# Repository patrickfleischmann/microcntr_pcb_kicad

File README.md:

# microcntr_pcb_kicad
PCB design files KiCad

[Kicanvas](https://kicanvas.org/?github=https%3A%2F%2Fgithub.com%2Fpatrickfleischmann%2Fmicrocntr_pcb_kicad%2Fblob%2F93434b71915ae8d7c4e8ab5cd5c0984640eee6fc%2Fmicrocntr.kicad_sch)

Application: KiCad (64-bit), Version: (6.0.7), release build

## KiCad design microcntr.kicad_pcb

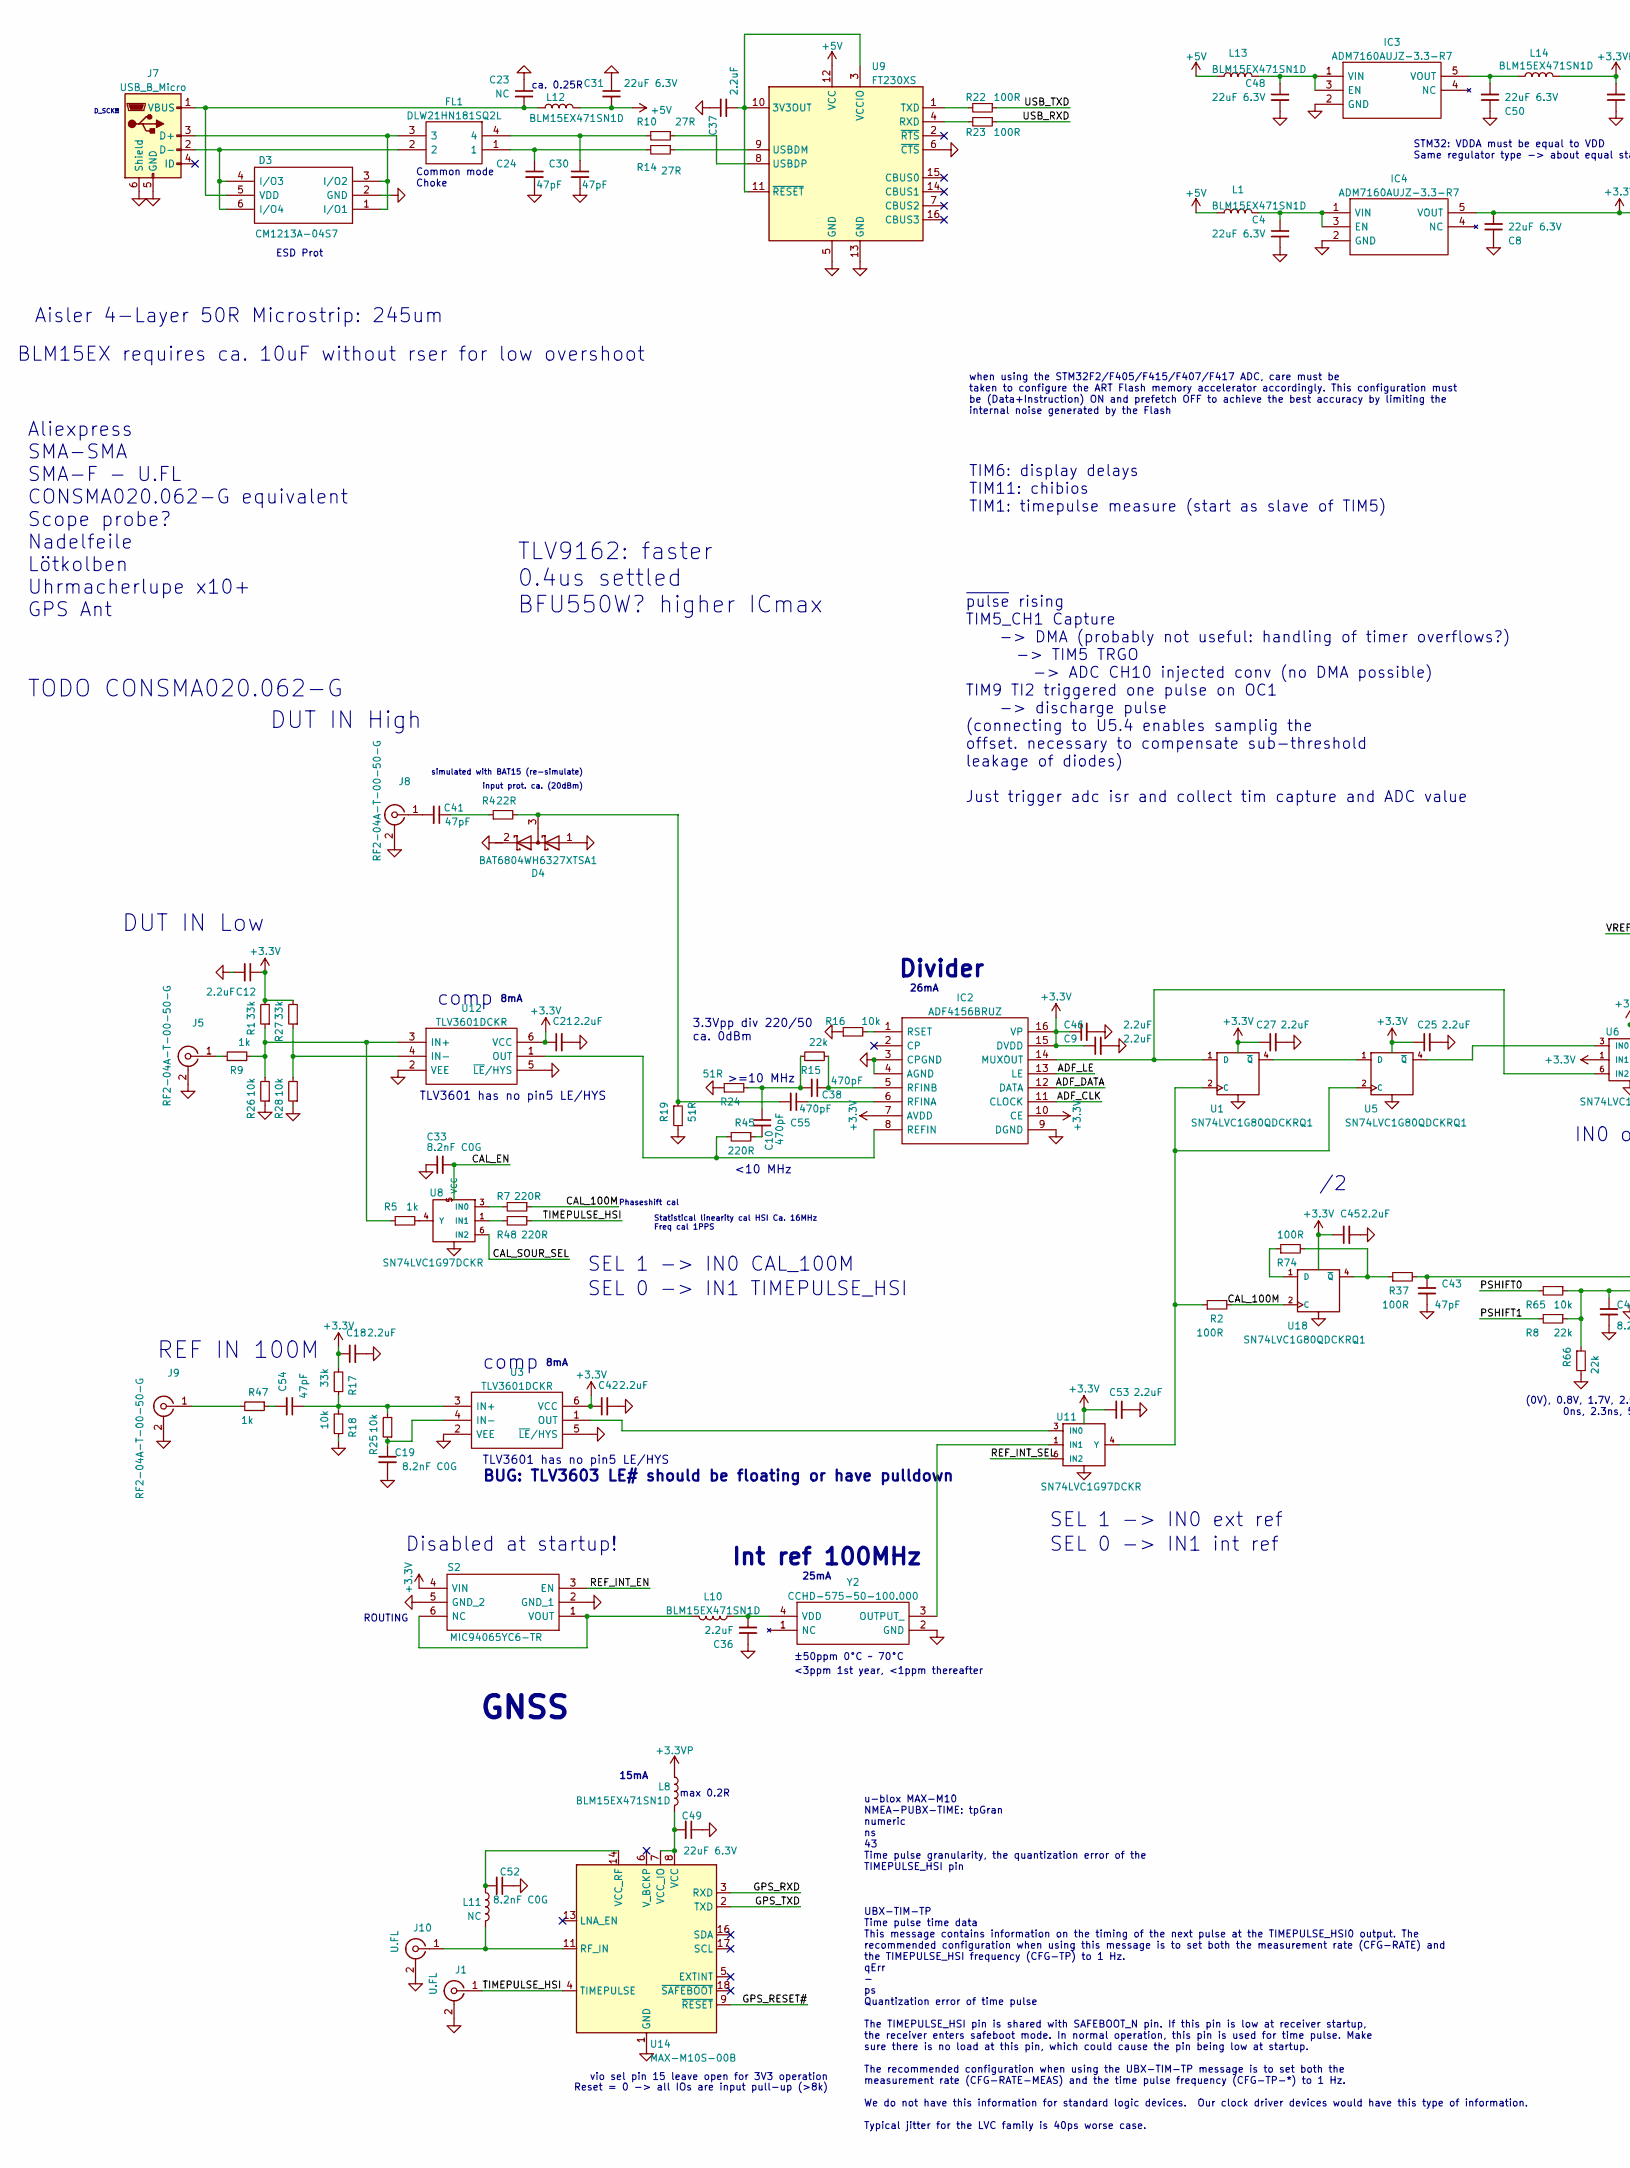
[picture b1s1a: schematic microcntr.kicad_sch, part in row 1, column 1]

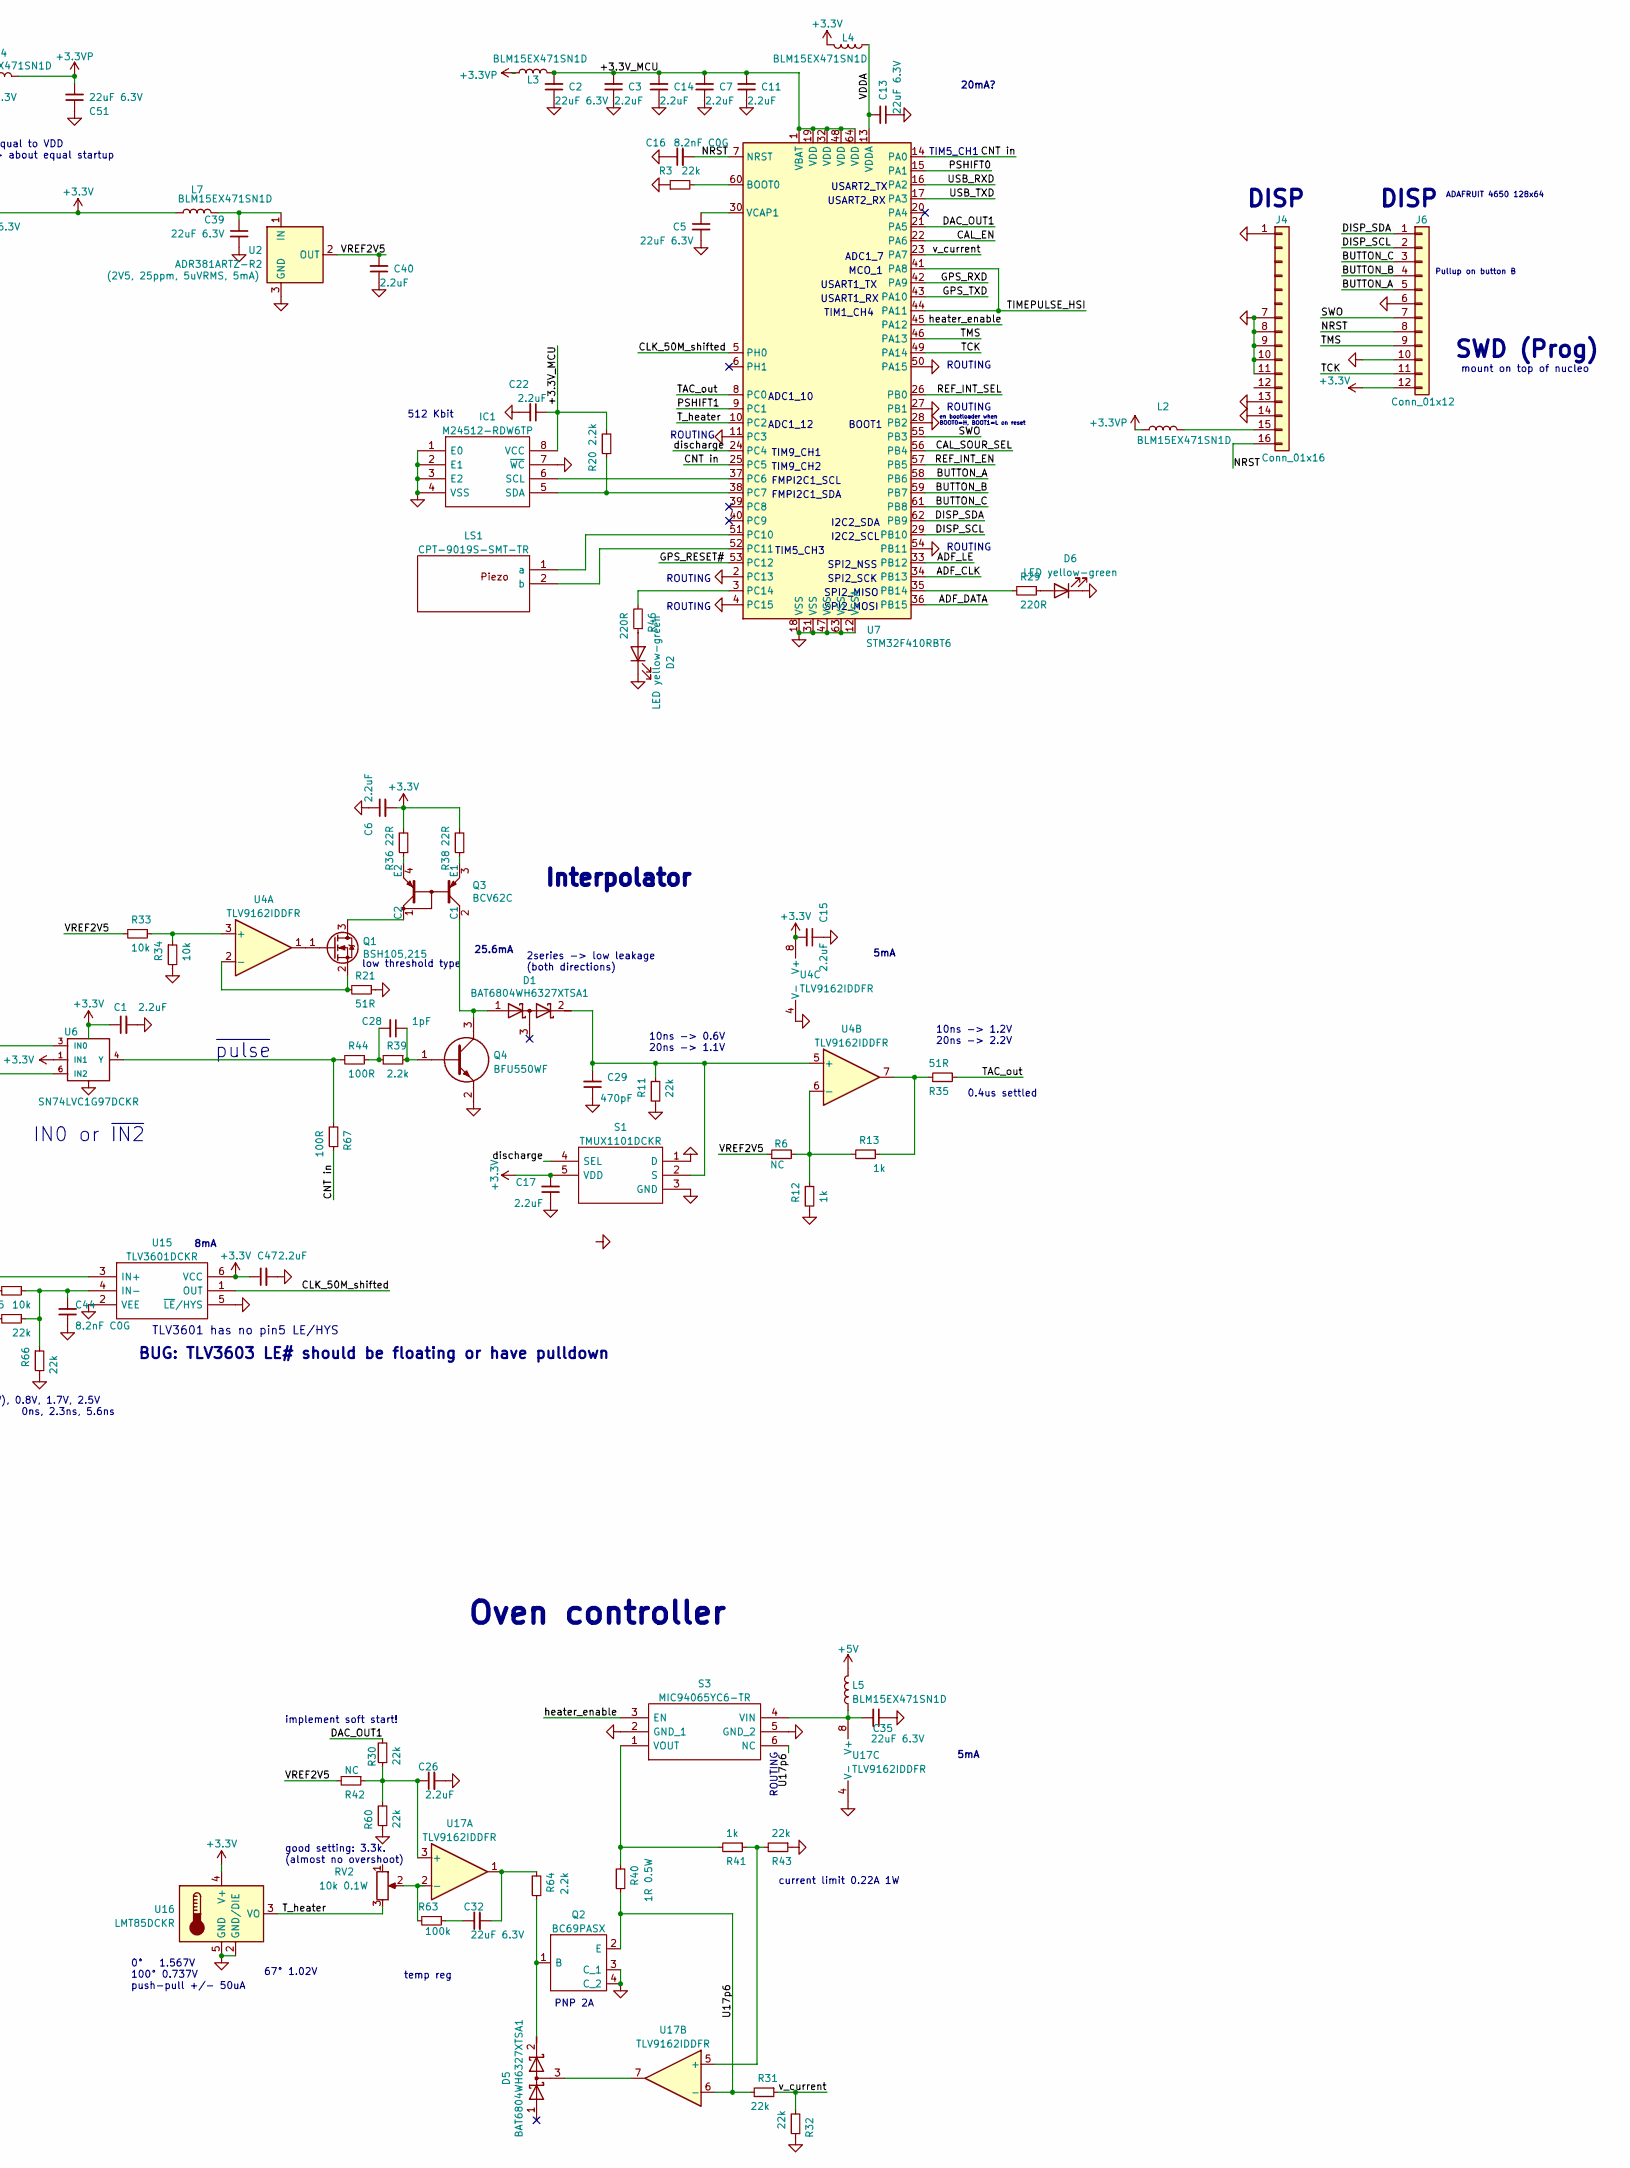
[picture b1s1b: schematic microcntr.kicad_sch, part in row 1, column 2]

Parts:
C1, C3, C6, C7, C9, C11, C12, C14, C15, C17, C18, C22, C25, C26, C27, C36, C37, C40, C45, C46, C47, C53: 2.2uF; C_0402_1005Metric; Manufacturer_Part_Number CL05A225MQ5NNNC; Digikey 1276-1469-1-ND
C2, C4, C5, C8, C13, C31, C32, C35, C39, C48, C49, C50, C51: 22uF 6.3V; C_0603_1608Metric; Manufacturer_Part_Number GRM188C80J226ME15; Digikey 490-10471-1-ND
C10, C38, C55: 470pF; C_0402_1005Metric
C16: 8.2nF C0G; C_0402_1005Metric; Manufacturer_Part_Number GRM1555C1H822JE01D; Digikey 1276-1469-1-ND
C19, C33, C41, C44, C52: 8.2nF C0G; C_0402_1005Metric; Manufacturer_Part_Number GRM1555C1H822JE01D; Digikey 490-GRM1555C1H822JE01DCT-ND
C21, C42: 2.2uF; R_0402_1005Metric; Manufacturer_Part_Number CL05A225MQ5NNNC; Digikey 1276-1469-1-ND
C23: NC; C_0402_1005Metric
C24, C30, C43, C54: 47pF; C_0402_1005Metric; Manufacturer_Part_Number CL05C470JB5NNNC; Digikey 1276-1699-1-ND
C28: 1pF; R_0402_1005Metric; Manufacturer_Part_Number CL05C010CB5NNNC; Digikey 1276-1595-1-ND
C29: 470pF; C_0402_1005Metric; Manufacturer_Part_Number 0402N471G500CT; Digikey 1292-1327-1-ND
D1, D4, D5: BAT6804WH6327XTSA1; SOT-323_SC-70; Manufacturer_Part_Number BAT6804WH6327XTSA1; Digikey BAT6804WH6327XTSA1CT-ND
D2, D6: LED yellow-green; LED_0402_1005Metric; Manufacturer_Part_Number B2841UYG-20D000514U1930; Digikey 3147-B2841UYG-20D000514U1930CT-ND
D3: CM1213A-04S7; SOT-363_SC-70-6; Mouser Part Number CM1213A−04S7
FL1: DLW21HN181SQ2L; DLW21HN121HQ2B; Mouser Part Number 81-DLW21HN181SQ2L
IC1: M24512-RDW6TP; SOP65P640X120-8N; Mouser Part Number 511-M24512-RDW6TP
IC2: ADF4156BRUZ; SOP65P640X120-16N; Mouser Part Number 584-ADF4156BRUZ
IC3, IC4: ADM7160AUJZ-3.3-R7; SOT95P280X100-5N; Mouser Part Number 584-ADM7160AUJZ3.3R7
J1, J10: U.FL; U.FL_Molex_MCRF_73412-0110_Vertical; Manufacturer_Part_Number 0734120110; Digikey WM5587CT-ND
J4: Conn_01x16; PinSocket_1x16_P2.54mm_Vertical
J5, J8, J9: RF2-04A-T-00-50-G; CONSMA020062G; Manufacturer_Part_Number RF2-04A-T-00-50-G
J6: Conn_01x12; PinSocket_1x12_P2.54mm_Vertical
J7: USB_B_Micro; USB_Micro-B_Amphenol_10103594-0001LF_Horizontal; Manufacturer_Part_Number 10103594-0001LF; Digikey 609-4050-1-ND
L1, L2, L3, L4, L5, L7, L8, L10, L12, L13, L14: BLM15EX471SN1D; L_0402_1005Metric; Manufacturer_Part_Number BLM15EX471SN1D; Digikey 490-BLM15EX471SN1DCT-ND
L11: NC; L_0402_1005Metric
LS1: CPT-9019S-SMT-TR; CPT9019SSMTTR; Mouser Part Number 490-CPT-9019S-SMT-TR
Q1: BSH105,215; SOT-23; Manufacturer_Part_Number BSH105,215; Digikey 1727-4924-1-ND
Q2: BC69PASX; Mouser Part Number 771-BC69PASX
Q3: BCV62C; SOT-143; Manufacturer_Part_Number BCV62CE6327HTSA1; Digikey BCV62CE6327HTSA1CT-ND
Q4: BFU550WF; SOT65P210X110-3N; Mouser Part Number 771-BFU550WF
R1, R17, R27: 33k; R_0402_1005Metric; Manufacturer_Part_Number RT0402FRE0733KL; Digikey YAG5933CT-ND
R2: 100R; R_0402_1005Metric; Manufacturer_Part_Number RT0402FRE07100RL; Digikey 13-RT0402FRE07220RLCT-ND
R3, R8, R11, R15, R30, R31, R32, R43, R60, R66: 22k; R_0402_1005Metric; Manufacturer_Part_Number RT0402FRE0722KL; Digikey YAG5931CT-ND
R4, R36, R38: 22R; R_0402_1005Metric; Manufacturer_Part_Number RT0402FRE0722KL; Digikey YAG5931CT-ND
R5: 1k; R_0402_1005Metric; Manufacturer_Part_Number RT0402FRE0710KL; Digikey YAG1233CT-ND
R6: NC; R_0402_1005Metric; Digikey YAG1233CT-ND
R7, R29, R45, R46, R48: 220R; R_0402_1005Metric; Manufacturer_Part_Number RT0402FRE07220RL; Digikey 13-RT0402FRE07220RLCT-ND
R9, R12, R41: 1k; R_0402_1005Metric; Manufacturer_Part_Number RT0402FRE071KL; Digikey YAG1234CT-ND
R10, R14: 27R; R_0402_1005Metric; Manufacturer_Part_Number RT0402FRE0751RL; Digikey YAG3343CT-ND
R13: 1k; R_0402_1005Metric; Manufacturer_Part_Number RT0402FRE071KL; Digikey 13-RT0402FRE072K2LCT-ND
R16, R18, R25, R26, R28, R33, R34, R65: 10k; R_0402_1005Metric; Manufacturer_Part_Number RT0402FRE0710KL; Digikey YAG1233CT-ND
R19, R21, R24, R35: 51R; R_0402_1005Metric; Manufacturer_Part_Number RT0402FRE0751RL; Digikey 13-RT0402FRE0751RLCT-ND
R20, R39, R64: 2.2k; R_0402_1005Metric; Manufacturer_Part_Number RT0402FRE072K2L; Digikey 13-RT0402FRE072K2LCT-ND
R22, R23, R37, R44, R67, R74: 100R; R_0402_1005Metric; Manufacturer_Part_Number RT0402FRE07100RL; Digikey YAG3342CT-ND
R40: 1R 0.5W; R_0805_2012Metric; Manufacturer_Part_Number ERJ-6DQJ1R0V; Digikey P19220CT-ND
R42: NC; R_0402_1005Metric; Manufacturer_Part_Number RT0402FRE0722KL; Digikey YAG5931CT-ND
R47: 1k; R_0402_1005Metric; Manufacturer_Part_Number YAG1234CT-ND; Digikey 13-RT0402FRE07220RLCT-ND
R63: 100k; R_0402_1005Metric; Manufacturer_Part_Number RT0402FRE07100KL; Digikey YAG2307CT-ND
RV2: 10k 0.1W; Potentiometer_Bourns_3214J_Horizontal; Manufacturer_Part_Number 3214J-2-103E; Digikey 118-3214J-2-103ECT-ND
S1: TMUX1101DCKR; SOT65P210X110-5N; Mouser Part Number 595-TMUX1101DCKR
S2, S3: MIC94065YC6-TR; SOT65P210X110-6N; Mouser Part Number 998-MIC94065YC6TR
U1, U5, U18: SN74LVC1G80QDCKRQ1; SOT-353_SC-70-5; Manufacturer_Part_Number SN74LVC1G80QDCKRQ1; Digikey 296-48165-1-ND
U2: ADR381ARTZ-R2; SOT-23; Manufacturer_Part_Number ADR381ARTZ-R2; Digikey 505-ADR381ARTZ-R2CT-ND
U3, U12, U15: TLV3601DCKR; SOT-363_SC-70-6; Mouser Part Number 595-TLV3603DCKR
U4, U17: TLV9162IDDFR; SOT65P280X110-8N; Manufacturer_Part_Number TLV9162IDDFR; Digikey 296-TLV9162IDDFRCT-ND
U6, U8, U11: SN74LVC1G97DCKR; SOT-363_SC-70-6; Manufacturer_Part_Number SN74LVC1G97DCKR; Digikey 296-15582-1-ND
U7: STM32F410RBT6; LQFP-64_10x10mm_P0.5mm; Manufacturer_Part_Number STM32F410RBT6; Digikey 497-16239-ND
U9: FT230XS; SSOP-16_3.9x4.9mm_P0.635mm; Manufacturer_Part_Number FT230XS-R; Digikey 768-1135-1-ND
U14: MAX-M10S-00B; ublox_MAX; Manufacturer_Part_Number MAX-M10S-00B; Digikey 672-MAX-M10S-00BCT-ND
U16: LMT85DCKR; SOT-353_SC-70-5; Manufacturer_Part_Number LMT85DCKR; Digikey 296-38164-1-ND
Y2: CCHD-575-50-100.000; CCHD57550100000; Mouser Part Number 549-CCHD-575-50-100

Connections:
+3.3V: C1.1, C6.2, C8.2, C9.1, C12.1, C15.2, C17.2, C18.1, C21.1, C25.1, C27.1, C42.1, C45.1, C46.1, C47.1, C53.1, IC2.7 (AVDD), IC2.10 (CE), IC2.15 (DVDD), IC2.16 (VP), IC4.5 (VOUT), J6.12, L4.2, L7.1, R1.2, R17.2, R27.2, R36.2, R38.2, S1.5 (VDD), S2.4 (VIN), U1.5 (VCC), U3.6 (VCC), U4.8 (V+), U5.5 (VCC), U6.1 (IN1), U6.5 (VCC), U11.5 (VCC), U12.6 (VCC), U15.6 (VCC), U16.4 (V+), U18.5 (VCC)
+3.3VP: C51.2, L2.1, L3.1, L8.2, L14.2
+5V: C31.2, L1.1, L5.2, L12.2, L13.1, U9.12 (VCC)
/+3.3V_MCU: C2.2, C3.2, C7.2, C11.2, C14.2, C22.1, IC1.8 (VCC), L3.2, R20.2, U7.1 (VBAT), U7.19 (VDD), U7.32 (VDD), U7.48 (VDD), U7.64 (VDD)
/ADF_CLK: IC2.11 (CLOCK), U7.34 (PB13)
/ADF_DATA: IC2.12 (DATA), U7.36 (PB15)
/ADF_LE: IC2.13 (LE), U7.33 (PB12)
/BUTTON_A: J6.5, U7.58 (PB6)
/BUTTON_B: J6.4, U7.59 (PB7)
/BUTTON_C: J6.3, U7.61 (PB8)
/CAL_100M: R2.2, R7.1, U18.2 (C)
/CAL_EN: C33.2, U7.22 (PA6), U8.5 (VCC)
/CAL_SOUR_SEL: U7.56 (PB4), U8.6 (IN2)
/CLK_50M_shifted: U7.5 (PH0), U15.1 (OUT)
/CNT in: R67.1, U7.14 (PA0), U7.25 (PC5)
/DAC_OUT1: R30.2, U7.21 (PA5)
/DISP_SCL: J6.2, U7.29 (PB10)
/DISP_SDA: J6.1, U7.62 (PB9)
/GPS_RESET#: U7.53 (PC12), U14.9 (~RESET)
/GPS_RXD: U7.42 (PA9), U14.3 (RXD)
/GPS_TXD: U7.43 (PA10), U14.2 (TXD)
/NRST: C16.2, J4.16, J6.8, U7.7 (NRST)
/PSHIFT0: R65.2, U7.15 (PA1)
/PSHIFT1: R8.2, U7.9 (PC1)
/REF_INT_EN: S2.3 (EN), U7.57 (PB5)
/REF_INT_SEL: U7.26 (PB0), U11.6 (IN2)
/SWO: J6.7, U7.55 (PB3)
/TAC_out: R35.2, U7.8 (PC0)
/TCK: J6.11, U7.49 (PA14)
/TIMEPULSE_HSI: J1.1 (In), R48.1, U7.41 (PA8), U7.44 (PA11), U14.4 (TIMEPULSE)
/TMS: J6.9, U7.46 (PA13)
/T_heater: RV2.3, U7.10 (PC2), U16.3 (VO)
/U17p6: Q2.2 (E), R31.2, R40.1, S3.6 (NC), U17.6 (-)
/USB_RXD: R23.1, U7.16 (PA2)
/USB_TXD: R22.1, U7.17 (PA3)
/VDDA: C13.2, L4.1, U7.13 (VDDA)
/VREF2V5: C40.2, R6.1, R33.2, R42.2, U2.2 (OUT)
/discharge: S1.4 (SEL), U7.24 (PC4)
/heater_enable: S3.3 (EN), U7.45 (PA12)
/v_current: R31.1, R32.2, U7.23 (PA7)
GND: C1.2, C2.1, C3.1, C4.2, C5.2, C6.1, C7.1, C8.1, C9.2, C11.1, C12.2, C13.1, C14.1, C15.1, C16.1, C17.1, C18.2, C19.2, C21.2, C22.2, C23.1, C24.2, C25.2, C26.2, C27.2, C29.1, C30.2, C31.1, C33.1, C35.1, C36.1, C37.1, C39.2, C40.1, C42.2, C43.1, C44.1, C45.2, C46.2, C47.2, C48.2, C49.1, C50.1, C51.1, C52.1, C53.2, D2.1 (K), D3.2 (GND), D4.1 (A), D4.2 (K), D6.1 (K), IC1.1 (E0), IC1.2 (E1), IC1.3 (E2), IC1.4 (VSS), IC1.7 (~WC), IC2.3 (CPGND), IC2.4 (AGND), IC2.9 (DGND), IC3.2 (GND), IC4.2 (GND), J1.2 (Ext), J4.1, J4.7, J4.8, J4.9, J4.10, J4.11, J4.13, J4.14, J5.2 (Ext), J6.6, J6.10, J7.5 (GND), J7.6 (Shield), J8.2 (Ext), J9.2 (Ext), J10.2 (Ext), Q2.3 (C_1), Q2.4 (C_2), Q4.2, R3.1, R11.2, R12.2, R16.1, R18.1, R19.2, R21.1, R24.1, R26.1, R28.1, R32.1, R34.2, R43.1, R60.1, R66.2, S1.1 (D), S1.3 (GND), S2.2 (GND_1), S2.5 (GND_2), S3.2 (GND_1), S3.5 (GND_2), U1.3 (GND), U2.3 (GND), U3.2 (VEE), U3.5 (~LE/HYS), U4.4 (V-), U5.3 (GND), U6.2 (GND), U7.2 (PC13), U7.4 (PC15), U7.11 (PC3), U7.12 (VSSA), U7.18 (VSS), U7.27 (PB1), U7.28 (PB2), U7.31 (VSS), U7.47 (VSS), U7.50 (PA15), U7.54 (PB11), U7.63 (VSS), U8.2 (GND), U9.5 (GND), U9.6 (~CTS), U9.13 (GND), U11.2 (GND), U12.2 (VEE), U12.5 (~LE/HYS), U14.1 (GND), U14.10 (GND), U14.12 (GND), U15.2 (VEE), U15.5 (~LE/HYS), U16.2 (GND/DIE), U16.5 (GND), U17.4 (V-), U18.3 (GND), Y2.2 (GND)
unnamed: C4.1, IC4.1 (VIN), IC4.3 (EN), L1.2
unnamed: C5.1, U7.30 (VCAP1)
unnamed: C10.1, C38.2, R15.1, R24.2
unnamed: C10.2, R45.1
unnamed: C19.1, R25.1, U3.4 (IN-)
unnamed: C23.2, D3.5 (VDD), J7.1 (VBUS), L12.1
unnamed: C24.1, FL1.1, R14.2
unnamed: C26.1, R30.1, R42.1, R60.2, U17.3 (+)
unnamed: C28.1, Q4.1, R39.1
unnamed: C28.2, R39.2, R44.1
unnamed: C29.2, D1.2 (K), R11.1, S1.2 (S), U4.5 (+)
unnamed: C30.1, FL1.4, R10.2
unnamed: C32.1, R63.1
unnamed: C32.2, R64.2, U17.1
unnamed: C35.2, L5.1, S3.4 (VIN), U17.8 (V+)
unnamed: C36.2, L10.2, Y2.4 (VDD)
unnamed: C37.2, U9.3 (VCCIO), U9.10 (3V3OUT), U9.11 (~RESET)
unnamed: C38.1, IC2.5 (RFINB), R15.2
unnamed: C39.1, L7.2, U2.1 (IN)
unnamed: C41.1, R4.1
unnamed: C41.2, J8.1 (In)
unnamed: C43.2, R37.2, U15.3 (IN+)
unnamed: C44.2, R8.1, R65.1, R66.1, U15.4 (IN-)
unnamed: C48.1, IC3.1 (VIN), IC3.3 (EN), L13.2
unnamed: C49.2, L8.1, U14.7 (VCC_IO), U14.8 (VCC)
unnamed: C50.2, IC3.5 (VOUT), L14.1
unnamed: C52.2, L11.2, U14.14 (VCC_RF)
unnamed: C54.1, R17.1, R18.2, R25.2, U3.3 (IN+)
unnamed: C54.2, R47.1
unnamed: C55.1, IC2.6 (RFINA)
unnamed: C55.2, D4.3 (common), R4.2, R19.1
unnamed: D1.1 (A), Q3.2 (C1), Q4.3
unnamed: D2.2 (A), R46.1
unnamed: D3.1 (I/O1), D3.3 (I/O2), FL1.3, J7.3 (D+)
unnamed: D3.4 (I/O3), D3.6 (I/O4), FL1.2, J7.2 (D-)
unnamed: D5.2 (K), Q2.1 (B), R64.1
unnamed: D5.3 (common), U17.7
unnamed: D6.2 (A), R29.1
unnamed: IC1.5 (SDA), R20.1, U7.38 (PC7)
unnamed: IC1.6 (SCL), U7.37 (PC6)
unnamed: IC2.1 (RSET), R16.2
unnamed: IC2.8 (REFIN), R45.2, U12.1 (OUT)
unnamed: IC2.14 (MUXOUT), U1.1 (D), U6.6 (IN2)
unnamed: J4.15, L2.2
unnamed: J5.1 (In), R9.1
unnamed: J9.1 (In), R47.2
unnamed: J10.1 (In), L11.1, U14.11 (RF_IN)
unnamed: L10.1, S2.1 (VOUT), S2.6 (NC)
unnamed: LS1.1 (a), U7.51 (PC10)
unnamed: LS1.2 (b), U7.52 (PC11)
unnamed: Q1.1 (G), U4.1
unnamed: Q1.2 (S), R21.2, U4.2 (-)
unnamed: Q1.3 (D), Q3.1 (C2)
unnamed: Q3.3 (E1), R38.1
unnamed: Q3.4 (E2), R36.1
unnamed: R1.1, R5.1, R9.2, R26.2, U12.3 (IN+)
unnamed: R2.1, U1.2 (C), U5.2 (C), U11.4 (Y)
unnamed: R3.2, U7.60 (BOOT0)
unnamed: R5.2, U8.4 (Y)
unnamed: R7.2, U8.3 (IN0)
unnamed: R10.1, U9.8 (USBDP)
unnamed: R6.2, R12.1, R13.2, U4.6 (-)
unnamed: R13.1, R35.1, U4.7
unnamed: R14.1, U9.9 (USBDM)
unnamed: R22.2, U9.1 (TXD)
unnamed: R23.2, U9.4 (RXD)
unnamed: R27.1, R28.2, U12.4 (IN-)
unnamed: R29.2, U7.35 (PB14)
unnamed: R33.1, R34.1, U4.3 (+)
unnamed: R37.1, R74.2, U18.4 (~Q)
unnamed: R40.2, R41.2, S3.1 (VOUT)
unnamed: R41.1, R43.2, U17.5 (+)
unnamed: R44.2, R67.2, U6.4 (Y)
unnamed: R46.2, U7.3 (PC14)
unnamed: R48.2, U8.1 (IN1)
unnamed: R63.2, RV2.2, U17.2 (-)
unnamed: R74.1, U18.1 (D)
unnamed: U1.4 (~Q), U5.1 (D)
unnamed: U5.4 (~Q), U6.3 (IN0)
unnamed: U11.1 (IN1), Y2.3 (OUTPUT_)
unnamed: U3.1 (OUT), U11.3 (IN0)

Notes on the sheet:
ADC1_10
comp
PNP 2A
512 Kbit
ADC1_7
ESD Prot
Pullup on button B
TLV3601 has no pin5 LE/HYS
temp reg
3.3Vpp div 220/50 ca. 0dBm
Statistical linearity cal HSI Ca. 16MHz Freq cal 1PPS
when using the STM32F2/F405/F415/F407/F417 ADC, care must be taken to configure the ART Flash memory accelerator accordingly. This configuration must be (Data+Instruction) ON and prefetch OFF to achieve the best accuracy by limiting the internal noise generated by the Flash
Oven controller
<3ppm 1st year, <1ppm thereafter
BUG: TLV3603 LE# should be floating or have pulldown
0° 1.567V 100° 0.737V push-pull +/- 50uA
SEL 0 -> IN1 int ref
(0V), 0.8V, 1.7V, 2.5V 0ns, 2.3ns, 5.6ns
D_SCK!!
input prot. ca. (20dBm)
SPI2_NSS
good setting: 3.3k. (almost no overshoot)
DUT IN Low
>=10 MHz
FMPI2C1_SDA
IN0 or ~{IN2}
TIM5_CH3
SWD (Prog)
SEL 1 -> IN0 CAL_100M
Disabled at startup!
SPI2_MISO
SPI2_MOSI
DISP
BOOT1
ROUTING
Interpolator
USART2_TX
TIM5_CH1
I2C2_SDA
Aisler 4-Layer 50R Microstrip: 245um

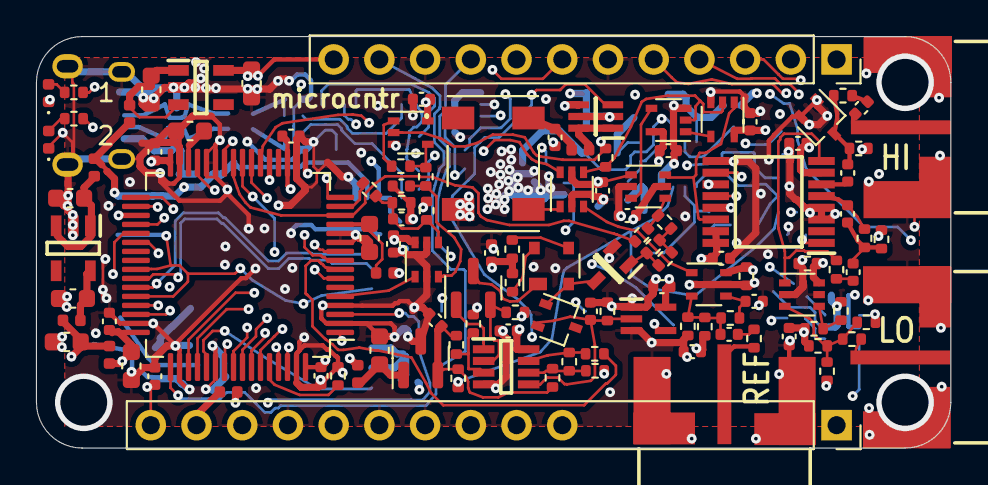
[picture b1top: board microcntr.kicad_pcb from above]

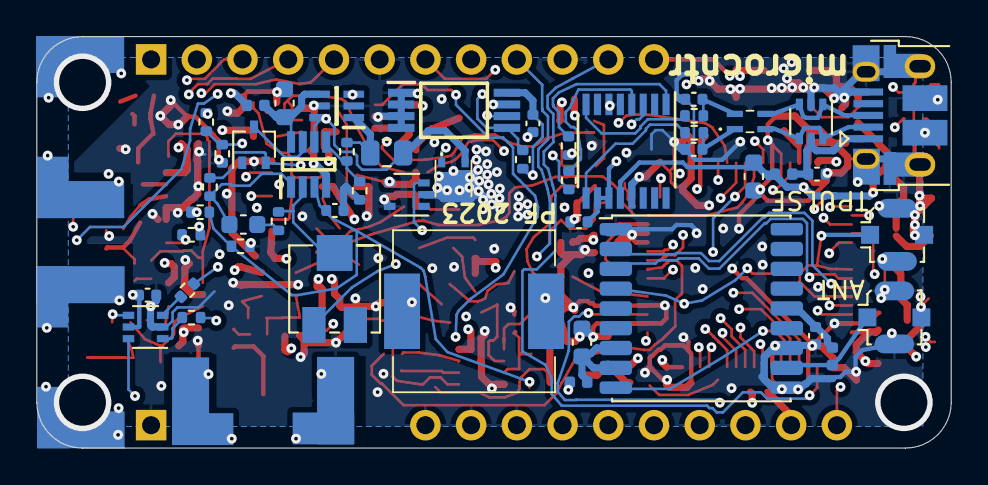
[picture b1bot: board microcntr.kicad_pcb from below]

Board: 6 copper layers, 50.8 x 22.9 mm, 165 parts (49 on the bottom side), 122 nets.

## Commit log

2023-09-30 initial
2023-09-30 corrected header rotation
2023-10-04 added buglist
2024-03-13 buglist new bugs
2024-03-17 added comments
2024-03-18 new buglist entries
2024-03-22 filled in buglist
2024-03-29 added comment
2024-06-12 some comments
